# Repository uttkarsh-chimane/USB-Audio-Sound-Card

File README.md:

<h1 align="center">⚡ PCM2706 USB Audio Sound Card</h1>

---

## ⚙️ What I Built

A compact USB-powered stereo audio sound card designed around the Texas Instruments PCM2706C USB Audio Codec. The device converts USB digital audio streams into analog stereo output and provides a simple plug-and-play audio interface for computers supporting the USB Audio Class standard.

---

## 🚀 Overview

This project implements a USB audio playback device using the PCM2706C USB audio codec. The design integrates USB communication, clock generation, analog audio filtering, and stereo output circuitry on a compact PCB developed in KiCad.

The board is powered directly from the USB port and outputs analog audio through a 3.5 mm audio jack.

---

## 📷 Project Gallery

🧩 **3D PCB Render**

🔌 **PCB Layout**

⚙️ **Schematic**

---

## 📑 Component Reference Sheet

The complete component reference sheet is available here:

📄 [Reference.xlsx](docs/reference.xlsx)

The spreadsheet contains:
- Reference Designators
- Quantity
- Component Values
- Package Information
- Footprint Assignments
- Brief Component Descriptions

---

## ✨ Features

* USB Audio Class compliant architecture
* PCM2706C USB audio codec
* USB bus powered (5 V)
* Stereo analog audio output
* Integrated RC output filtering network
* 12 MHz crystal clock source
* Compact PCB footprint
* Designed using KiCad

---

## ⚒️ Hardware Architecture

```
USB Host
    │
    ▼
USB Connector
    │
    ▼
PCM2706C USB Audio Codec
    │
    ▼
RC Output Filter
    │
    ▼
3.5 mm Stereo Audio Jack
```
---

## 🧠 Schematic Highlights

**USB Interface**

* USB D+ and D− lines routed through 22 Ω series resistors.
* Pull-up resistor used for USB device detection.
* USB bus-powered operation.

**Clock Generation**

* 12 MHz crystal oscillator connected to the PCM2706C.
* Load capacitors selected according to crystal requirements.

**Audio Output Stage**

* Analog left and right channels filtered using RC networks.
* AC coupling capacitors remove DC offset before audio output.
* Stereo output available through a 3.5 mm audio jack.

**Power Integrity**

* Dedicated decoupling capacitors placed near codec supply pins.
* Separate analog and digital supply filtering considerations included.

---

## 🧩 PCB Design Insights

The PCB was designed as a compact single-board implementation with:

* Short USB signal paths
* Local decoupling near the codec IC
* Crystal placement close to oscillator pins
* Dedicated analog output filtering section
* 3D mechanical verification using external component models

---

## 🧪 Applications

* USB-to-analog audio conversion
* External USB sound card prototyping
* Educational projects involving USB Audio Class devices
* Audio codec evaluation and experimentation
* Mixed-signal PCB design learning
* Embedded audio hardware development

---

## ⚠️ Limitations

This project is intended for educational and design demonstration purposes.

* No integrated headphone amplifier stage
* Design has not been physically fabricated or tested
* Intended primarily for line-level audio output

---

## 🚀 Future Improvements

* USB-C connector variant
* Headphone amplifier stage
* ESD protection circuitry
* Improved analog output filtering
* Revision B PCB optimization

---

## 🛠️ Design Software

* KiCad 10
* Custom and vendor-provided symbol libraries
* Vendor STEP/IGES mechanical models

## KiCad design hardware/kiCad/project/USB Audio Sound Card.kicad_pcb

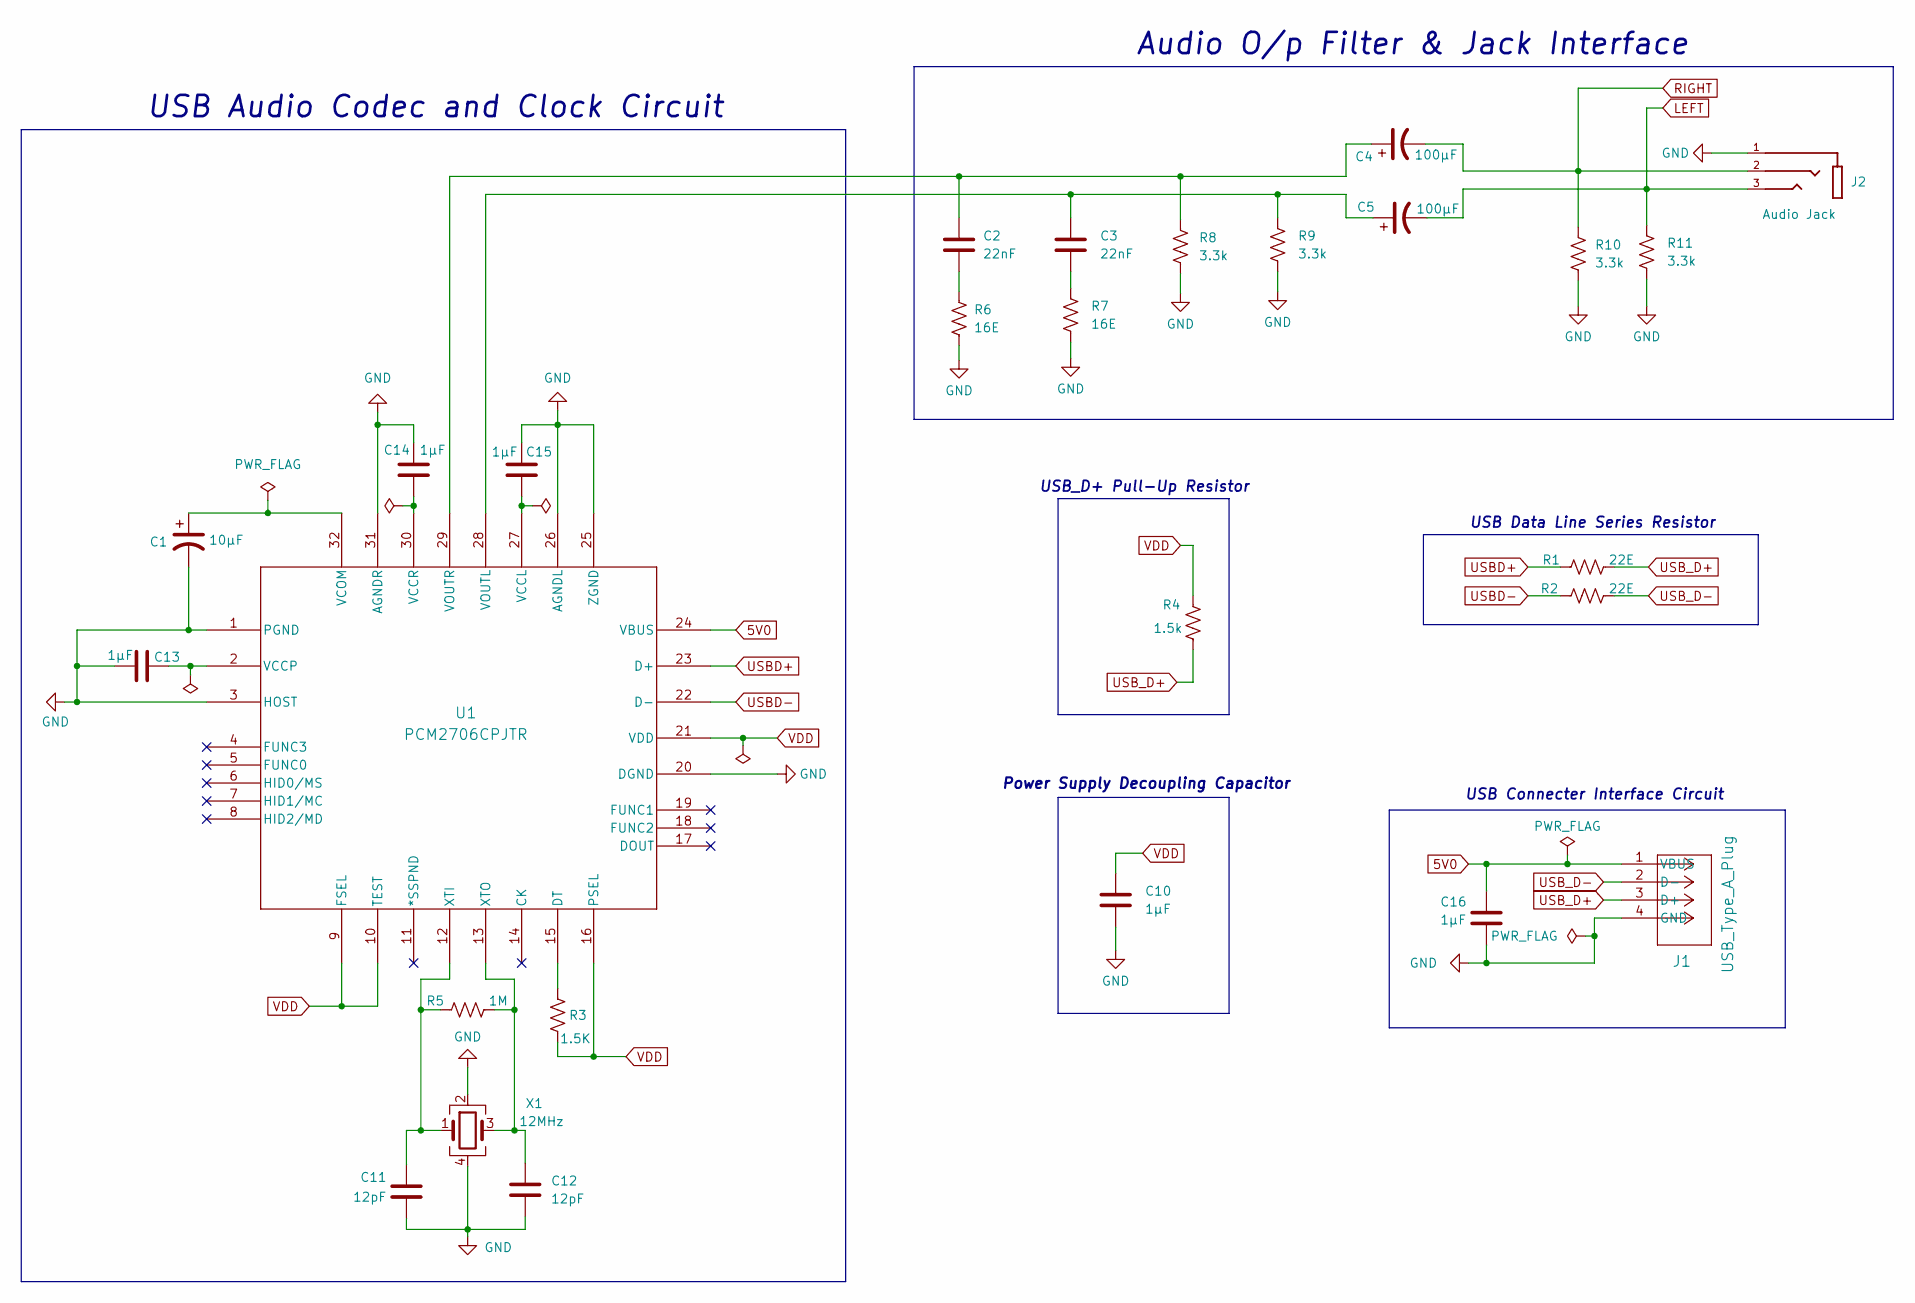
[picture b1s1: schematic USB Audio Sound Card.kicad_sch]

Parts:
C1: 10µF; CP_Radial_D5.0mm_P2.00mm
C2, C3: 22nF; C_0603_1608Metric_Pad1.08x0.95mm_HandSolder
C4, C5: 100µF; CP_Radial_D10.0mm_P5.00mm
C10, C13, C14, C15, C16: 1µF; R_0805_2012Metric_Pad1.20x1.40mm_HandSolder
C11, C12: 12pF; R_0603_1608Metric_Pad0.98x0.95mm_HandSolder
J1: USB_Type_A_Plug; MOLEX_48037-1000
J2: Audio Jack; KYCON_STX-3000; PARTREV D5; DigiKey_Part_Number 2092-STX-3000-ND
R1, R2: 22E; R_0603_1608Metric_Pad0.98x0.95mm_HandSolder
R3: 1.5K; R_0603_1608Metric_Pad0.98x0.95mm_HandSolder
R4: 1.5k; R_0603_1608Metric_Pad0.98x0.95mm_HandSolder
R5: 1M; R_0603_1608Metric_Pad0.98x0.95mm_HandSolder
R6, R7: 16E; R_0603_1608Metric_Pad0.98x0.95mm_HandSolder
R8, R9, R10, R11: 3.3k; R_0603_1608Metric_Pad0.98x0.95mm_HandSolder
U1: PCM2706CPJTR; PJT32
X1: 12MHz; Crystal_SMD_Abracon_ABM8AIG-4Pin_3.2x2.5mm

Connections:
5V0: C16.1, J1.1 (VBUS), U1.24 (VBUS)
GND: C1.2, C10.2, C11.2, C12.2, C13.1, C14.1, C15.1, C16.2, J1.4 (GND), J2.1, R6.2, R7.2, R8.2, R9.2, R10.2, R11.2, U1.1 (PGND), U1.3 (HOST), U1.20 (DGND), U1.25 (ZGND), U1.26 (AGNDL), U1.31 (AGNDR), X1.2, X1.4
LEFT: C5.2, J2.3, R11.1
unnamed: C2.2, R6.1
unnamed: C3.2, R7.1
unnamed: R3.1, U1.15 (DT)
unnamed: C15.2, U1.27 (VCCL)
unnamed: C13.2, U1.2 (VCCP)
unnamed: C14.2, U1.30 (VCCR)
unnamed: C1.1, U1.32 (VCOM)
unnamed: C3.1, C5.1, R9.1, U1.28 (VOUTL)
unnamed: C2.1, C4.1, R8.1, U1.29 (VOUTR)
unnamed: C11.1, R5.2, U1.12 (XTI), X1.1
unnamed: C12.1, R5.1, U1.13 (XTO), X1.3
RIGHT: C4.2, J2.2, R10.1
USBD+: R1.1, U1.23 (D+)
USBD-: R2.1, U1.22 (D-)
USB_D+: J1.3 (D+), R1.2, R4.1
USB_D-: J1.2 (D-), R2.2
VDD: C10.1, R3.2, R4.2, U1.9 (FSEL), U1.10 (TEST), U1.16 (PSEL), U1.21 (VDD)

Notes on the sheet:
USB_D+ Pull-Up Resistor
USB Audio Codec and Clock Circuit
USB Data Line Series Resistor
USB Connecter Interface Circuit
Power Supply Decoupling Capacitor
Audio O/p Filter & Jack Interface

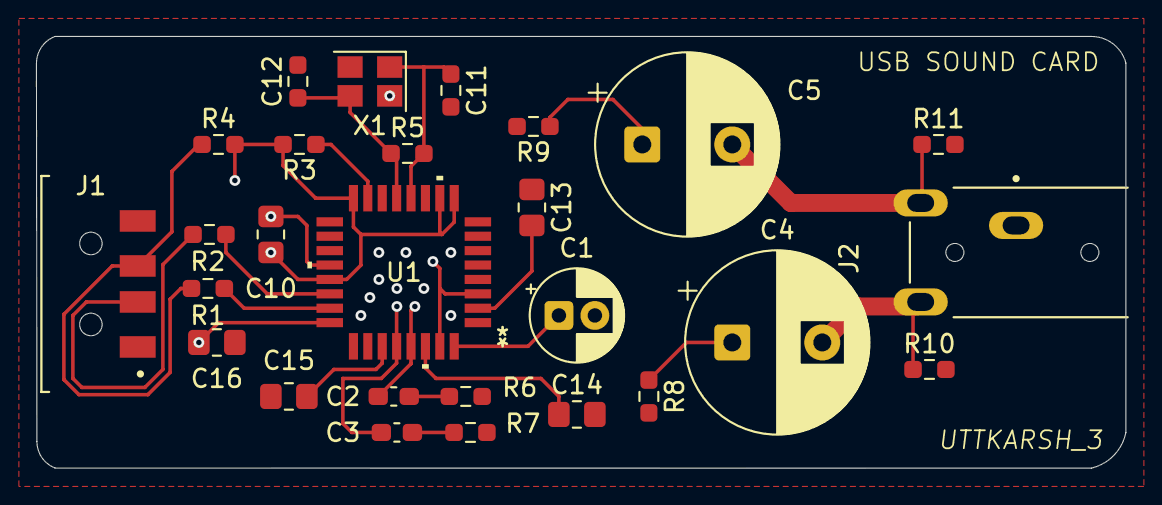
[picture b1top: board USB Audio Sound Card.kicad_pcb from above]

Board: 2 copper layers, 60.5 x 24.0 mm, 27 parts (0 on the bottom side), 20 nets.

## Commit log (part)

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2026-05-30 Initial commit: USB Audio Sound Card project
